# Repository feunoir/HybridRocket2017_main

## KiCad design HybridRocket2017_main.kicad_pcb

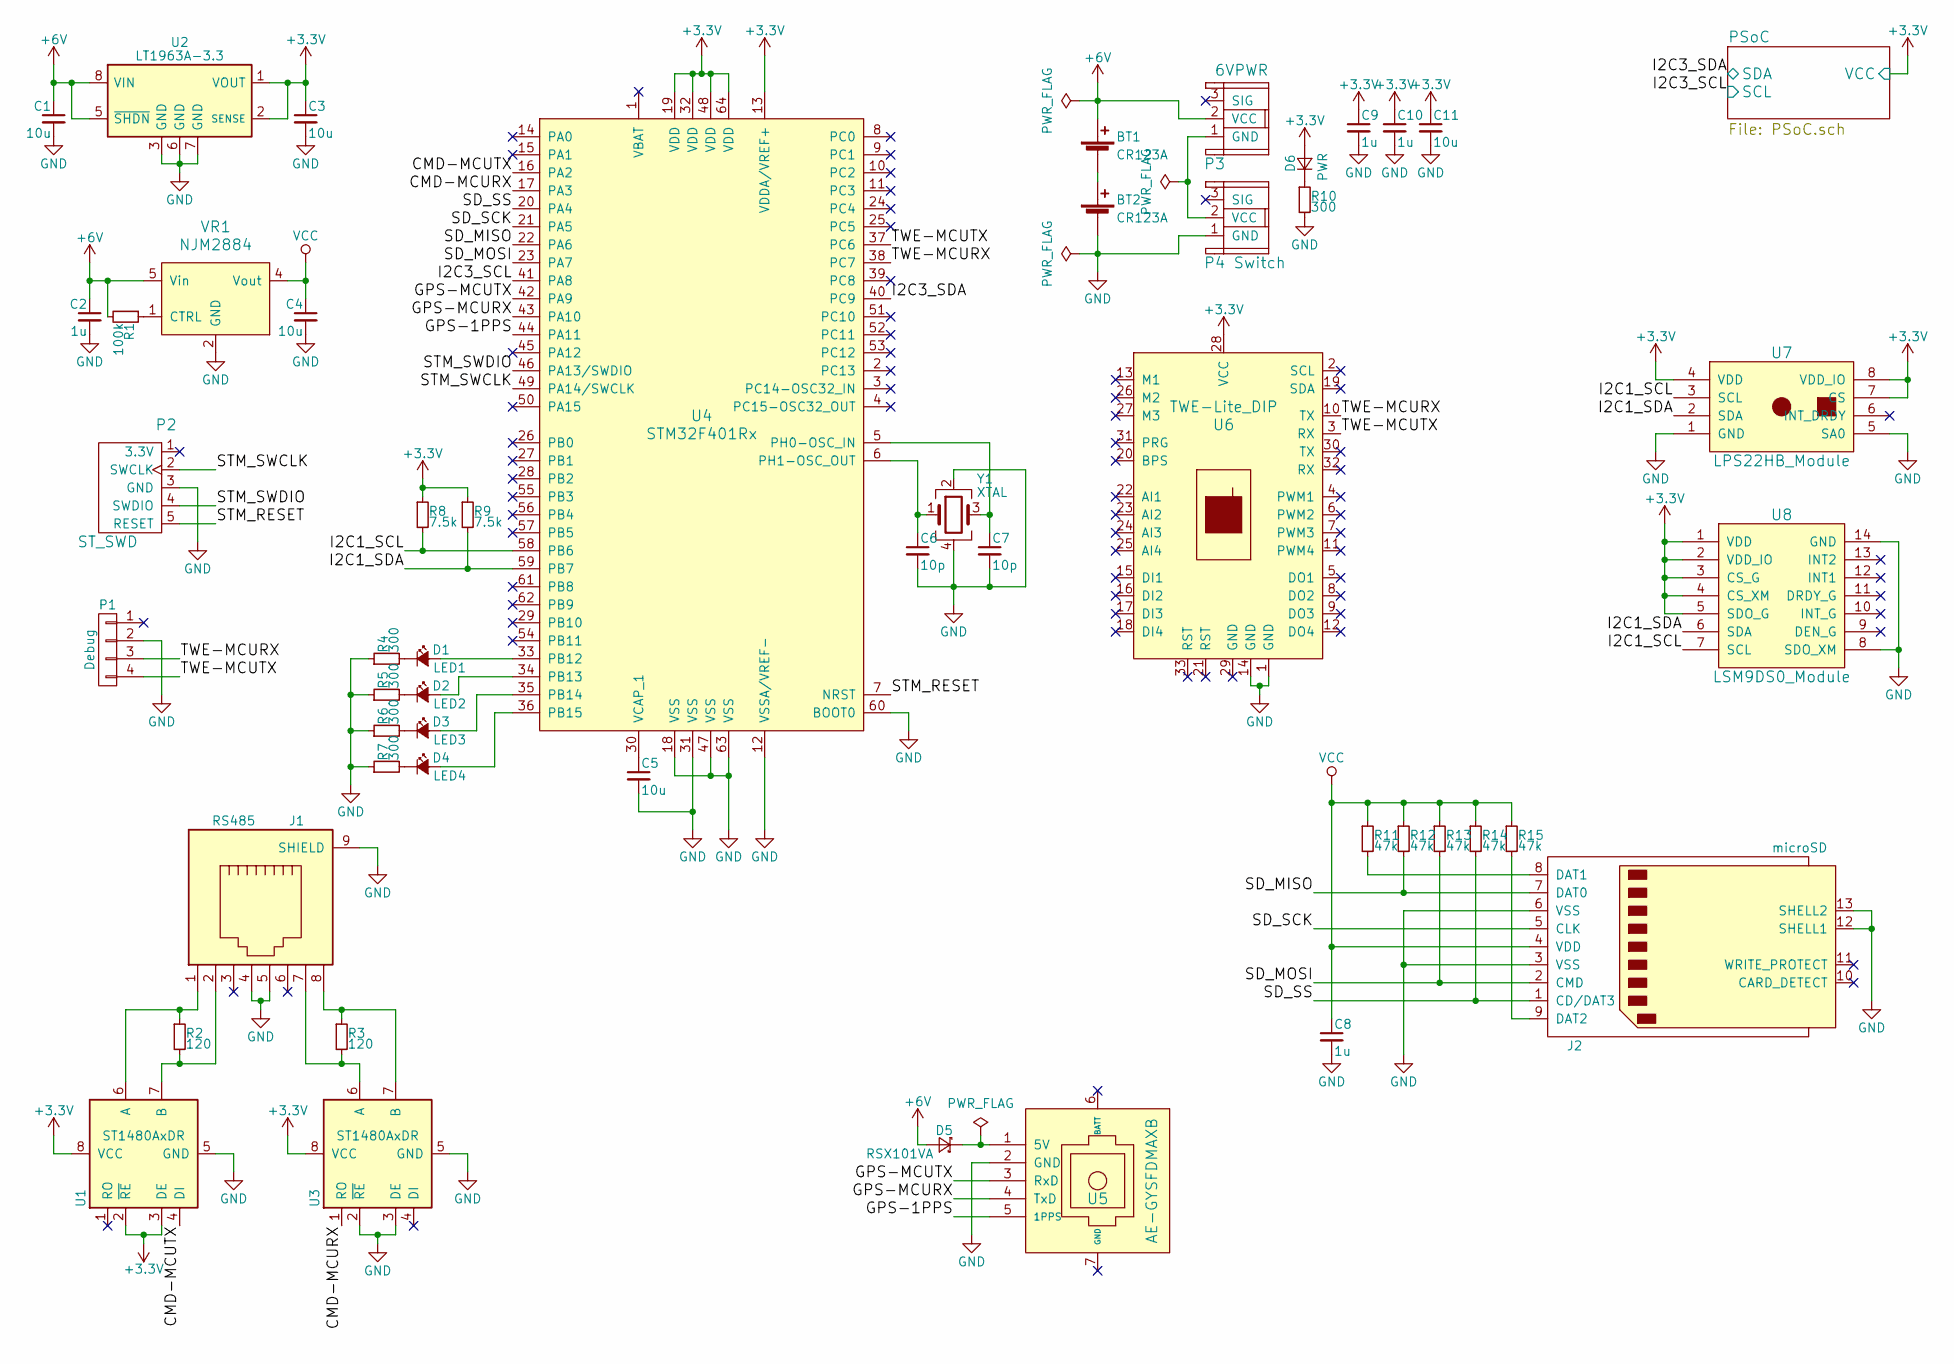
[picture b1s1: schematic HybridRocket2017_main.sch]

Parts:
BT1, BT2: CR123A; BHC-CR123A
C1, C3, C4, C5, C11: 10u; C_0805
C2, C8, C9, C10: 1u; C_0805
C6, C7: 10p; C_0603
D1: LED1; LED_0603
D2: LED2; LED_0603
D3: LED3; LED_0603
D4: LED4; LED_0603
D5: RSX101VA; D_TUMD2
D6: PWR; LED_0603
J1: RS485; 7810-8P8C
J2: microSD; microSD_DM3AT-SFPEJ
P1: Debug; Pin_Header_Straight_1x04_Pitch2.54mm
P2: ST_SWD; DF1E-5P_Straight
P3: 6VPWR; DF1E-3P_Straight
P4: Switch; DF1E-3P_Straight
R1: 100k; R_0603_HandSoldering
R2, R3: 120; R_0603_HandSoldering
R4, R5, R6, R7, R10: 300; R_0603_HandSoldering
R8, R9: 7.5k; R_1206
R11, R12, R13, R14, R15: 47k; R_0603_HandSoldering
U1, U3: ST1480AxDR; SOIC-8_3.9x4.9mm_Pitch1.27mm
U2: LT1963A-3.3; SOIC-8_3.9x4.9mm_Pitch1.27mm
U4: STM32F401Rx; LQFP-64_10x10mm_Pitch0.5mm
U5: AE-GYSFDMAXB
U6: TWE-Lite_DIP; TWE-Lite_DIP_28P
U7: LPS22HB_Module; Strawberry-Linux_Module_8P
U8: LSM9DS0_Module; DIP-14_W7.62mm
VR1: NJM2884; SOT-89-5
Y1: XTAL; Crystal_SMD_SeikoEpson_FA238-4pin_3.2x2.5mm_HandSoldering

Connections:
+3V3: C3.1, C9.1, C10.1, C11.1, D6.2 (A), R8.1, R9.1, U1.2 (~RE~), U1.3 (DE), U1.8 (VCC), U2.1 (VOUT), U2.2 (SENSE), U3.8 (VCC), U4.13 (VDDA/VREF+), U4.19 (VDD), U4.32 (VDD), U4.48 (VDD), U4.64 (VDD), U6.28 (VCC), U7.4 (VDD), U7.7 (CS), U7.8 (VDD_IO), U8.1 (VDD), U8.2 (VDD_IO), U8.3 (CS_G), U8.4 (CS_XM), U8.5 (SDO_G); also elsewhere on the board
+6V: BT1.1 (+), C1.1, C2.1, D5.2 (A), P3.2 (VCC), R1.2, U2.5 (~SHDN), U2.8 (VIN), VR1.5 (Vin)
/CMD-MCURX: U3.1 (RO), U4.17 (PA3)
/CMD-MCUTX: U1.4 (DI), U4.16 (PA2)
/GPS-1PPS: U4.44 (PA11), U5.5 (1PPS)
/GPS-MCURX: U4.43 (PA10), U5.4 (TxD)
/GPS-MCUTX: U4.42 (PA9), U5.3 (RxD)
/I2C1_SCL: R8.2, U4.58 (PB6), U7.3 (SCL), U8.7 (SCL)
/I2C1_SDA: R9.2, U4.59 (PB7), U7.2 (SDA), U8.6 (SDA)
/I2C3_SCL: U4.41 (PA8); also elsewhere on the board
/I2C3_SDA: U4.40 (PC9); also elsewhere on the board
/SD_MISO: J2.7 (DAT0), R12.2, U4.22 (PA6)
/SD_MOSI: J2.2 (CMD), R13.2, U4.23 (PA7)
/SD_SCK: J2.5 (CLK), U4.21 (PA5)
/SD_SS: J2.1 (CD/DAT3), R14.2, U4.20 (PA4)
/STM_RESET: P2.5 (RESET), U4.7 (NRST)
/STM_SWCLK: P2.2 (SWCLK), U4.49 (PA14/SWCLK)
/STM_SWDIO: P2.4 (SWDIO), U4.46 (PA13/SWDIO)
/TWE-MCURX: P1.3, U4.38 (PC7), U6.10 (TX)
/TWE-MCUTX: P1.4, U4.37 (PC6), U6.3 (RX)
GND: BT2.2 (-), C1.2, C2.2, C3.2, C4.2, C5.2, C6.2, C7.2, C8.2, C9.2, C10.2, C11.2, J1.4, J1.5, J1.9 (SHIELD), J2.3 (VSS), J2.6 (VSS), J2.12 (SHELL1), J2.13 (SHELL2), P1.2, P2.3 (GND), P4.1 (GND), R4.1, R5.1, R6.1, R7.1, R10.2, U1.5 (GND), U2.3 (GND), U2.6 (GND), U2.7 (GND), U3.2 (~RE~), U3.3 (DE), U3.5 (GND), U4.12 (VSSA/VREF-), U4.18 (VSS), U4.31 (VSS), U4.47 (VSS), U4.60 (BOOT0), U4.63 (VSS), U5.2 (GND), U6.1 (GND), U6.14 (GND), U7.1 (GND), U7.5 (SA0), U8.8 (SDO_XM), U8.14 (GND), VR1.2 (GND), Y1.2, Y1.4; also elsewhere on the board
unnamed: BT1.2 (-), BT2.1 (+)
unnamed: C5.1, U4.30 (VCAP_1)
unnamed: C6.1, U4.6 (PH1-OSC_OUT), Y1.1
unnamed: C7.1, U4.5 (PH0-OSC_IN), Y1.3
unnamed: D1.1 (K), R4.2
unnamed: D1.2 (A), U4.33 (PB12)
unnamed: D2.1 (K), R5.2
unnamed: D2.2 (A), U4.34 (PB13)
unnamed: D3.1 (K), R6.2
unnamed: D3.2 (A), U4.35 (PB14)
unnamed: D4.1 (K), R7.2
unnamed: D4.2 (A), U4.36 (PB15)
unnamed: D5.1 (K), U5.1 (5V)
unnamed: D6.1 (K), R10.1
unnamed: J1.1, R2.1, U1.6 (A)
unnamed: J1.2, R2.2, U1.7 (B)
unnamed: J1.7, R3.2, U3.6 (A)
unnamed: J1.8, R3.1, U3.7 (B)
unnamed: J2.8 (DAT1), R11.2
unnamed: J2.9 (DAT2), R15.2
unnamed: P3.1 (GND), P4.2 (VCC)
unnamed: R1.1, VR1.1 (CTRL)
VCC: C4.1, C8.1, J2.4 (VDD), R11.1, R12.1, R13.1, R14.1, R15.1, VR1.4 (Vout)

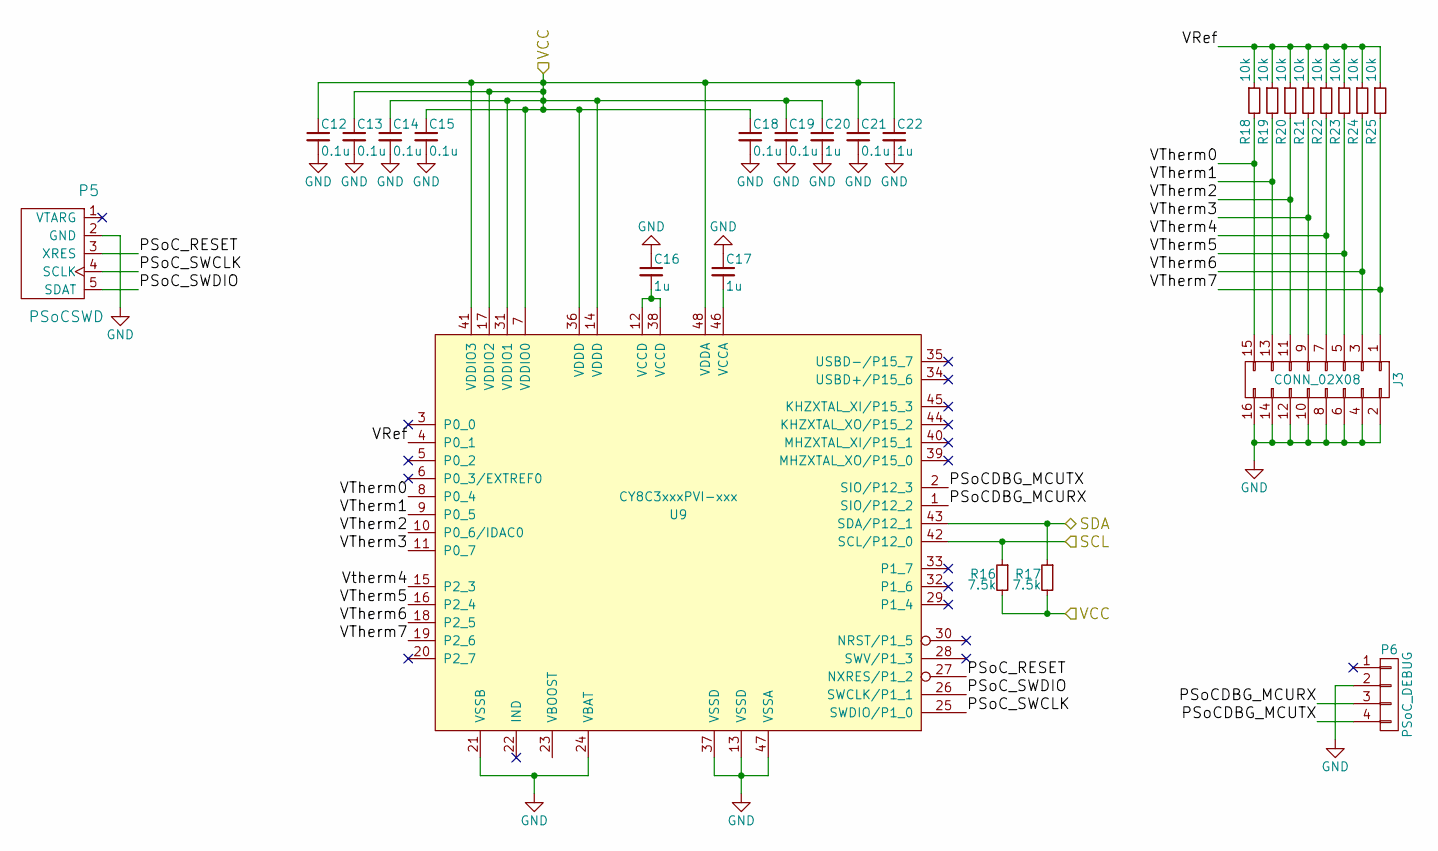
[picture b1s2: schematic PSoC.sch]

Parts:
C12, C13, C14, C15, C18, C19, C21: 0.1u; C_0603
C16, C17, C20, C22: 1u; C_0805
J3: CONN_02X08
P5: PSoCSWD; 05JQ-BT
P6: PSoC_DEBUG; Pin_Header_Straight_1x04_Pitch2.54mm
R16, R17: 7.5k; R_1206
R18, R19, R20, R21, R22, R23, R24, R25: 10k; R_0603_HandSoldering
U9: CY8C3xxxPVI-xxx; MODULE

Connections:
+3V3: C12.1, C13.1, C14.1, C15.1, C18.1, C19.1, C20.1, C21.1, C22.1, R16.2, R17.2, U9.7 (VDDIO0), U9.14 (VDDD), U9.17 (VDDIO2), U9.31 (VDDIO1), U9.36 (VDDD), U9.41 (VDDIO3), U9.48 (VDDA); also elsewhere on the board
/I2C3_SCL: R16.1, U9.42 (SCL/P12_0); also elsewhere on the board
/I2C3_SDA: R17.1, U9.43 (SDA/P12_1); also elsewhere on the board
/PSoC/PSoCDBG_MCURX: P6.3, U9.1 (SIO/P12_2)
/PSoC/PSoCDBG_MCUTX: P6.4, U9.2 (SIO/P12_3)
/PSoC/PSoC_RESET: P5.3 (XRES), U9.27 (NXRES/P1_2)
/PSoC/PSoC_SWCLK: P5.4 (SCLK), U9.25 (SWDIO/P1_0)
/PSoC/PSoC_SWDIO: P5.5 (SDAT), U9.26 (SWCLK/P1_1)
/PSoC/VRef: R18.1, R19.1, R20.1, R21.1, R22.1, R23.1, R24.1, R25.1, U9.4 (P0_1)
/PSoC/VTherm0: J3.15, R18.2, U9.8 (P0_4)
/PSoC/VTherm1: J3.13, R19.2, U9.9 (P0_5)
/PSoC/VTherm2: J3.11, R20.2, U9.10 (P0_6/IDAC0)
/PSoC/VTherm3: J3.9, R21.2, U9.11 (P0_7)
/PSoC/VTherm4: J3.7, R22.2, U9.15 (P2_3)
/PSoC/VTherm5: J3.5, R23.2, U9.16 (P2_4)
/PSoC/VTherm6: J3.3, R24.2, U9.18 (P2_5)
/PSoC/VTherm7: J3.1, R25.2, U9.19 (P2_6)
GND: C12.2, C13.2, C14.2, C15.2, C16.1, C17.1, C18.2, C19.2, C20.2, C21.2, C22.2, J3.2, J3.4, J3.6, J3.8, J3.10, J3.12, J3.14, J3.16, P5.2 (GND), P6.2, U9.13 (VSSD), U9.21 (VSSB), U9.24 (VBAT), U9.37 (VSSD), U9.47 (VSSA); also elsewhere on the board
unnamed: C16.2, U9.12 (VCCD), U9.38 (VCCD)
unnamed: C17.2, U9.46 (VCCA)

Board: 2 copper layers, 74 parts (8 on the bottom side), 60 nets, no tracks yet.

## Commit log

2017-03-10 :circus_tent: Added .gitattributes & .gitignore files
2017-03-10 firstcommit
